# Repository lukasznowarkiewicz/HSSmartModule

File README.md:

# HSSmartModule

## Overview

This repository contains design files of Home Span Smart Module. The device is intended to use with existing electrical installation as a light controller. Initially intended to be flashed with Home Span firmware and  use with Apple Home Kit ecosystem. This will allow basic support of the implement features like outputs control, reading states form the inputs and control from other devices - aka smart home in-wall module functionality. This will allow rather quick start of the desting of the device in the files and give chance to spot potential problems right away. In the future it is planned to create custom application, with support for all implemented features in hardware like power measurement, input from presence sensor and enabling thread radio communication. The device intentionally is divided into two PCBs. This will allow independent testing, of high voltage and low voltage parts. In the future will be possible to replace low voltage PCB with with another variant - equiped with another MCU, for example NRF52840. In the future after initial bringup, set of boards could be easily redesigned as single rigid-flex PCB. 

## Features

- Powered form 230VAC mains voltage
- 2x output for controlling 230VAC devices, up to 4A per channel
- 3x 230VAC inputs - two intended for ordinary switches for direct control of the outputs, additional input for motion or presence sensor
- Power usage measurement using CS5480
- ESP32-C6 SOC as main MCU and radio module
- 8MB SPI flash memory 
- Wi-Fi 6, Bluetooth 5 LE, Thread (802.15.4), Zigbee
- U.FL antenna connector

## Block diagram

## Low Voltage PCB

### LVPCB Schematic

- 3V3 power input - board is powered from HVPCB, or from programmer. If HVPCB is supplying power, 3V3 power jumper on HSSM-Prog should be left unconnected. 

- ESP32-C6 microcontroller - controlls outputs, reads values from inputs, controlls LEDs and communicate with other devices over thread, zigbee or wifi. All power inputs, crystal oscillator circuit, connection to SPI flash implemented according to datasheet.

- Antenna connector - allow connecting external 2.4 GHz antenna for wirelless connectivity

- SPI flash memory - stores ESP32-C6 program

- Additional switches and outs for debug - as program development with board powered from 230VAC seems risky, added additional switches and LEDs representing inputs and outputs on HVPCB. With those program development is possible, even without HVPCB, while LVPCB beeing powered from 3V3 LDO on programming board. 

- Programming connector - to connect HSSM-Prog, enables UART communication and puting ESP32-C6 into programming mode

- Edge connector - allows HSSM-FCB to be soldered to and connect HVPCB

## High Voltage PCB

<!-- 

 -->

Features:
- Outputs controls - two relays for switching 230VAC loads, internally connected to live wire terminal. Both relays powered from 12V 

- Input switches - three 230VAC inputs - for 

- 230VAC to 12VDC

- 12VDC to 3V3VDC converter

- Power measurement

## Flexible circuit board

## HSSmartModule Programmer

Features
- CP2102N USB UART converter
- Automatically put ESP32 chips into programming mode 
- power supply and data lines insulation 
- 6 poles 1.27 mm header and 6 poles 2.54 mm header for programming
- 3V3 voltage supplied to target MCU can be disable by removal of the jumper

## Manufacturing

All PCBs manufactured by JLCPCB, according to stackup set in each board's project.  

### HSSM-Prog

### HSSM-LVPCB

### HSSM-HVPCB

## Boards bring up 

## HSSM device assembly

### Firmware for boards testing

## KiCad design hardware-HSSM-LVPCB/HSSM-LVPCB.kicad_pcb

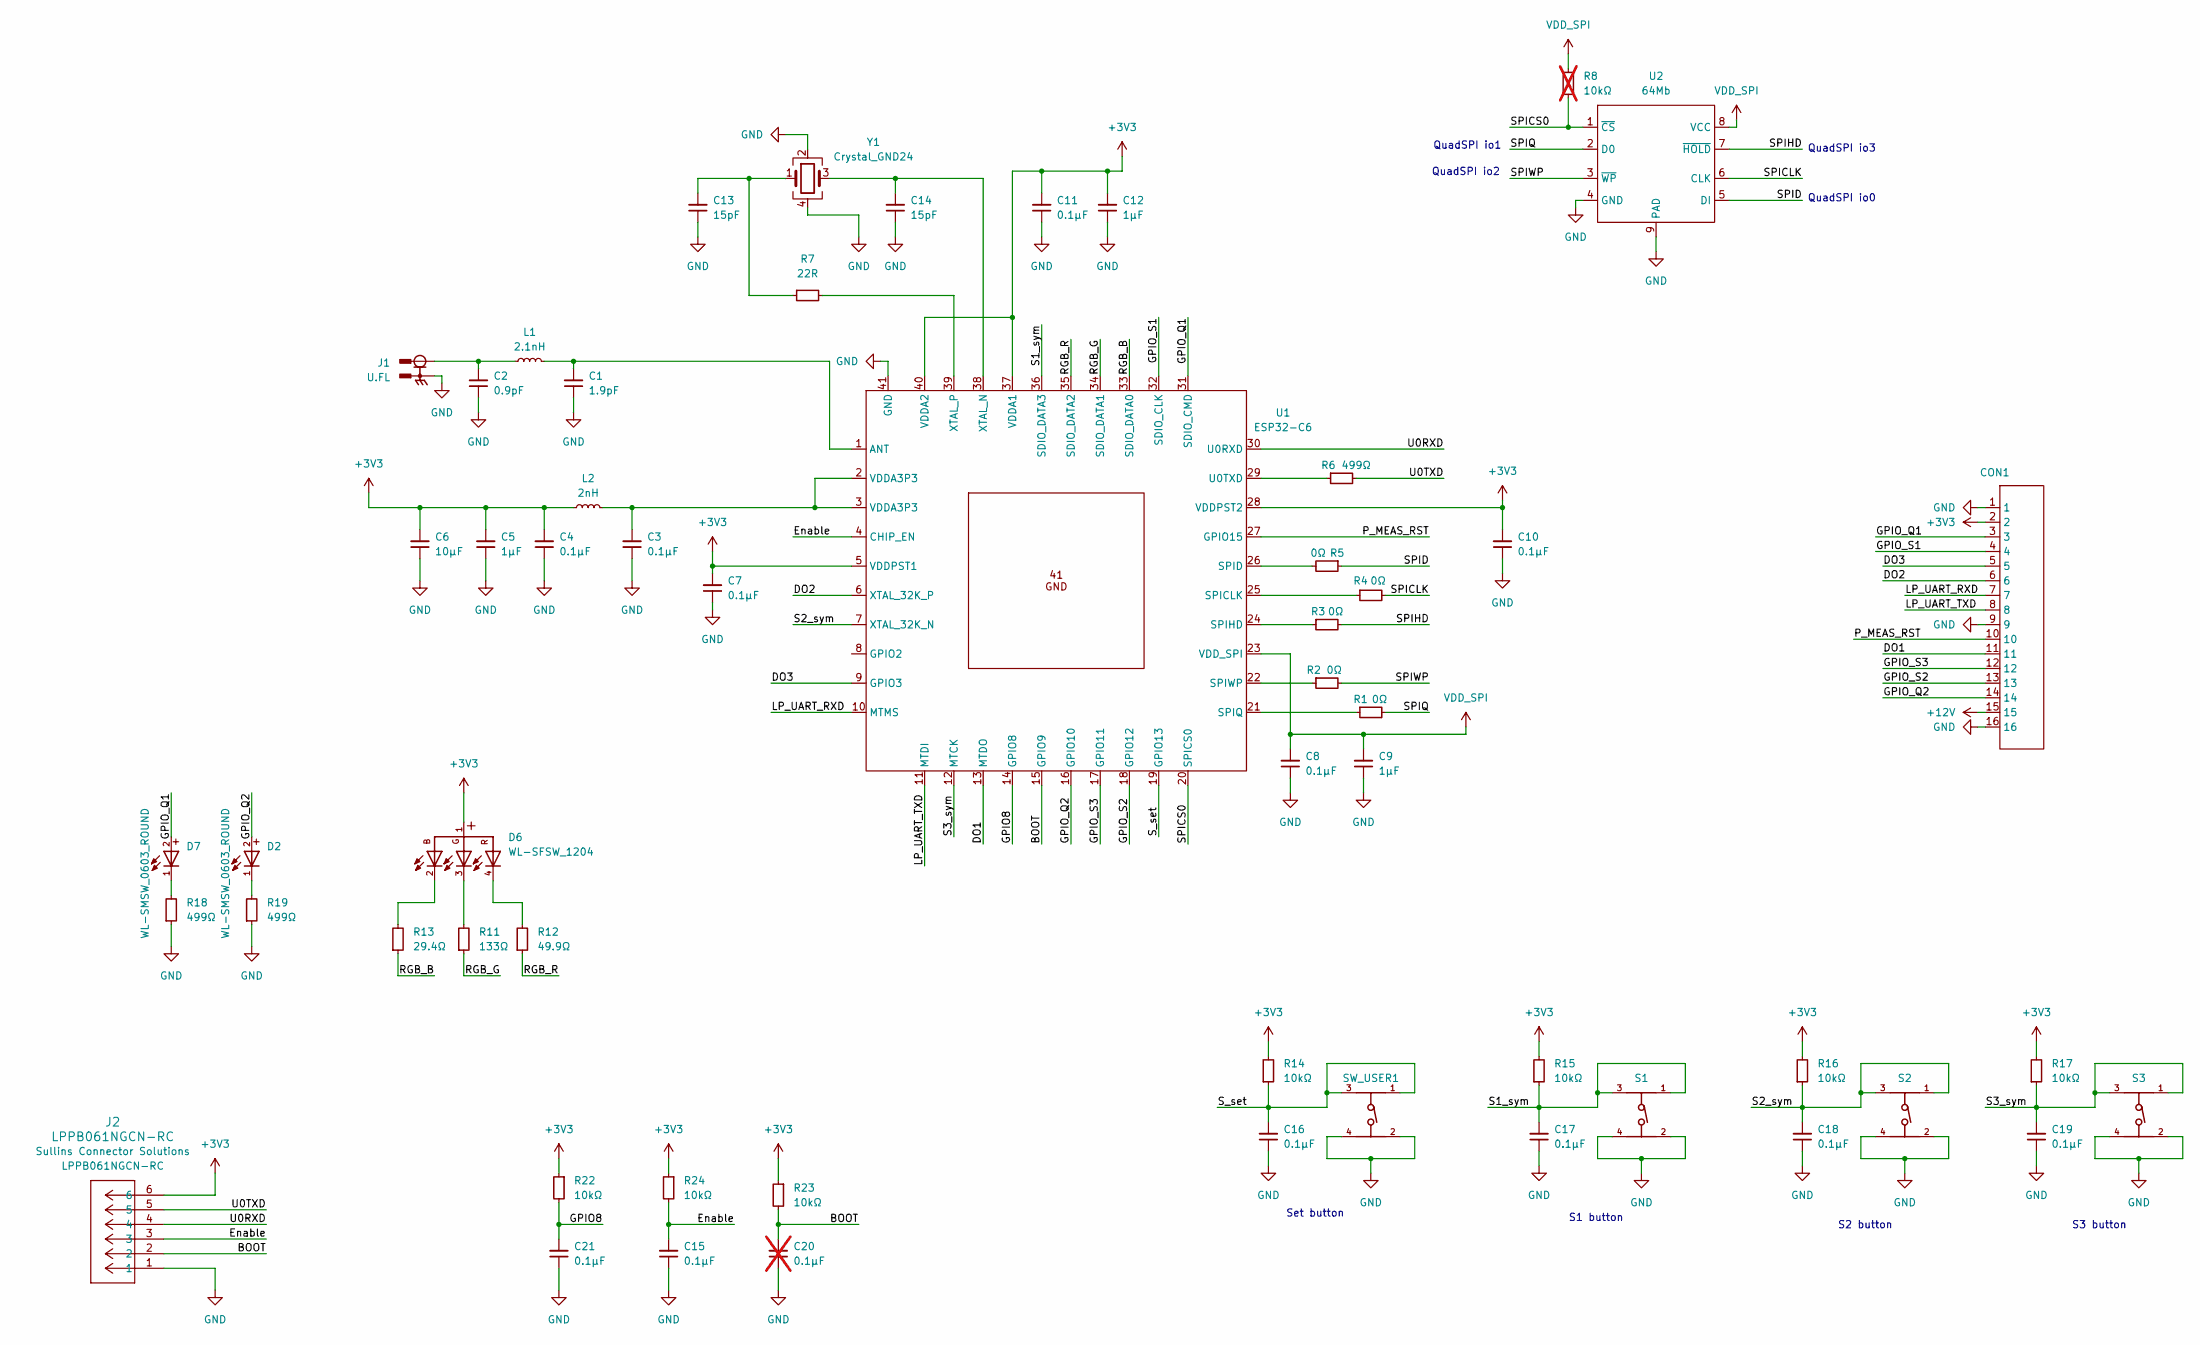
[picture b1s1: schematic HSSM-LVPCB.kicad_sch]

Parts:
C1: C_1p9_0.05pct_50V_0201_GRM0335C1H1R9WA01D; C_0201; MPN GRM0335C1H1R9WA01D
C2: C_0p9_0.05pct_50V_0201_GRM0335C1HR90WA01D; C_0201; MPN GRM0335C1HR90WA01D
C3, C4, C7, C8, C10, C11, C15, C16, C17, C18, C19, C21: C_0u1_10pct_50V_0402_GRM155R71H104KE14D; C_0402; MPN GRM155R71H104KE14D
C5, C9, C12: C_1uF_10pct_16V_0603_GCM188R71C105KA64D; C_0603; MPN GCM188R71C105KA64D
C6: C_10u_20pct_16V_0603_GRM188R61C106MA73D; C_0603; MPN GRM188R61C106MA73D
C13, C14: C_15pF_1pct_50V_0402_C0402C150F5GACAUTO; C_0402; MPN C0402C150F5GACAUTO
C20: C_0u1_10pct_50V_0402_GRM155R71H104KE14D; C_0402; MPN GRM155R71H104KE14D; not fitted
CON1: FFC_solder_connector_16pos
D2, D7: WL-SMSW_0603_ROUND; 155060AS73200; MPN 155060AS73200
D6: WL-SFSW_1204; 155124M173200; MPN 155124M173200
J1: UFL_R_SMT_1_10; CONMHF1-SMD-T; MPN U.FL-R-SMT-1(10)
J2: LPPB061NGCN-RC; MPN LPPB061NGCN-RC
L1: L_2n1_2000mA_0201_LQP03HQ2N1B02D; L_0201; MPN LQP03HQ2N1B02D
L2: L_2nH_0402_ MHQ1005075HA2N0BTD25; L_0402; MPN MHQ1005075HA2N0BTD25
R1, R2, R3, R4, R5: R_0R_5pct_0402_RC0402JR-070RL; R_0402; MPN RC0402JR-070RL
R6, R18, R19: R_499R_1pct_0402_RC0402FR-07499RL; R_0402; MPN RC0402FR-07499RL
R7: R_22R_1pct_0402_CRCW040222R0FKED; R_0402; MPN CRCW040222R0FKED
R8: R_10k_1pct_0402_RC0402FR-0710KL; R_0402; MPN RC0402FR-0710KL; not fitted
R11: R_133R_1pct_0402_CRCW0402133RFKED; R_0402; MPN CRCW0402133RFKED
R12: R_49R9_1pct_0402_CRCW040249R9FKED; R_0402; MPN CRCW040249R9FKED
R13: R_29R4_1pct_0402_CRCW040229R4FKED; R_0402; MPN CRCW040229R4FKED
R14, R15, R16, R17, R22, R23, R24: R_10k_1pct_0402_RC0402FR-0710KL; R_0402; MPN RC0402FR-0710KL
S1, S2, S3: 434331045822; MPN 434331045822
SW_USER1: 434331045822; MPN 434331045822
U1: ESP32-C6; QFN-40-1EP_5x5mm_P0.4mm_EP3.6x3.6mm; MPN ESP32-C6
U2: W25Q64JVZPIM_WSON-8; WSON-8-1EP_6x5mm_P1.27mm_EP3.4x4.3mm; MPN W25Q64JVZPIM
Y1: Crystal_GND24; Crystal_SMD_2016-4Pin_2.0x1.6mm; MPN CN4040M00010001

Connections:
+3V3: C4.2, C5.2, C6.2, C7.2, C10.2, C11.2, C12.2, CON1.2, D6.1, J2.6, L2.1, R14.2, R15.2, R16.2, R17.2, R22.1, R23.1, R24.1, U1.5 (VDDPST1), U1.28 (VDDPST2), U1.37 (VDDA1), U1.40 (VDDA2)
+12V: CON1.15
/BOOT: C20.2, J2.2, R23.2, U1.15 (GPIO9)
/DO1: CON1.11, U1.13 (MTDO)
/DO2: CON1.6, U1.6 (XTAL_32K_P)
/DO3: CON1.5, U1.9 (GPIO3)
/Enable: C15.2, J2.3, R24.2, U1.4 (CHIP_EN)
/GPIO8: C21.2, R22.2, U1.14 (GPIO8)
/GPIO_Q1: CON1.3, D7.2, U1.31 (SDIO_CMD)
/GPIO_Q2: CON1.14, D2.2, U1.16 (GPIO10)
/GPIO_S1: CON1.4, U1.32 (SDIO_CLK)
/GPIO_S2: CON1.13, U1.18 (GPIO12)
/GPIO_S3: CON1.12, U1.17 (GPIO11)
/LP_UART_RXD: CON1.7, U1.10 (MTMS)
/LP_UART_TXD: CON1.8, U1.11 (MTDI)
/P_MEAS_RST: CON1.10, U1.27 (GPIO15)
/RGB_B: R13.1, U1.33 (SDIO_DATA0)
/RGB_G: R11.1, U1.34 (SDIO_DATA1)
/RGB_R: R12.1, U1.35 (SDIO_DATA2)
/S1_sym: C17.2, R15.1, S1.1, S1.3, U1.36 (SDIO_DATA3)
/S2_sym: C18.2, R16.1, S2.1, S2.3, U1.7 (XTAL_32K_N)
/S3_sym: C19.2, R17.1, S3.1, S3.3, U1.12 (MTCK)
/SPICLK: R4.2, U2.6 (CLK)
/SPICS0: R8.1, U1.20 (SPICS0), U2.1 (~CS)
/SPID: R5.1, U2.5 (DI)
/SPIHD: R3.2, U2.7 (~HOLD)
/SPIQ: R1.2, U2.2 (D0)
/SPIWP: R2.2, U2.3 (~WP)
/S_set: C16.2, R14.1, SW_USER1.1, SW_USER1.3, U1.19 (GPIO13)
/U0RXD: J2.4, U1.30 (U0RXD)
/U0TXD: J2.5, R6.2
GND: C1.1, C2.1, C3.1, C4.1, C5.1, C6.1, C7.1, C8.1, C9.1, C10.1, C11.1, C12.1, C13.1, C14.1, C15.1, C16.1, C17.1, C18.1, C19.1, C20.1, C21.1, CON1.1, CON1.9, CON1.16, J1.S1, J1.S2, J1.S3, J2.1, R18.1, R19.1, S1.2, S1.4, S2.2, S2.4, S3.2, S3.4, SW_USER1.2, SW_USER1.4, U1.41 (GND), U2.4 (GND), U2.9 (PAD), Y1.2, Y1.4
unnamed: C2.2, J1.1, L1.1
unnamed: C3.2, L2.2, U1.2 (VDDA3P3), U1.3 (VDDA3P3)
unnamed: C13.2, R7.1, Y1.1
unnamed: D2.1, R19.2
unnamed: D6.2, R13.2
unnamed: D6.3, R11.2
unnamed: D6.4, R12.2
unnamed: D7.1, R18.2
unnamed: C1.2, L1.2, U1.1 (ANT)
unnamed: R4.1, U1.25 (SPICLK)
unnamed: R5.2, U1.26 (SPID)
unnamed: R3.1, U1.24 (SPIHD)
unnamed: R1.1, U1.21 (SPIQ)
unnamed: R2.1, U1.22 (SPIWP)
unnamed: R6.1, U1.29 (U0TXD)
unnamed: C14.2, U1.38 (XTAL_N), Y1.3
unnamed: R7.2, U1.39 (XTAL_P)
VDD_SPI: C8.2, C9.2, R8.2, U1.23 (VDD_SPI), U2.8 (VCC)

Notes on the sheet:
QuadSPI io3
Set button
S1 button
QuadSPI io2
QuadSPI io1
QuadSPI io0
S2 button
S3 button

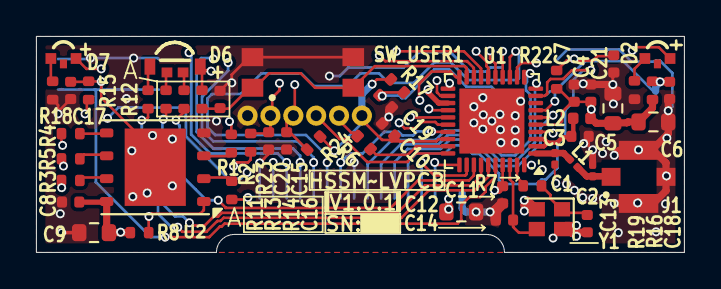
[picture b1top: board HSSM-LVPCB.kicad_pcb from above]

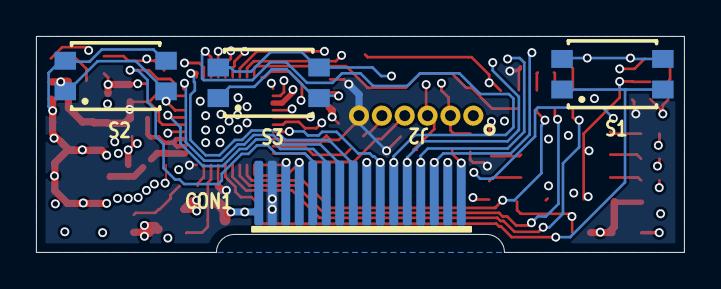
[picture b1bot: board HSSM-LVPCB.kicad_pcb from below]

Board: 4 copper layers, 36.0 x 12.0 mm, 56 parts (5 on the bottom side), 49 nets.

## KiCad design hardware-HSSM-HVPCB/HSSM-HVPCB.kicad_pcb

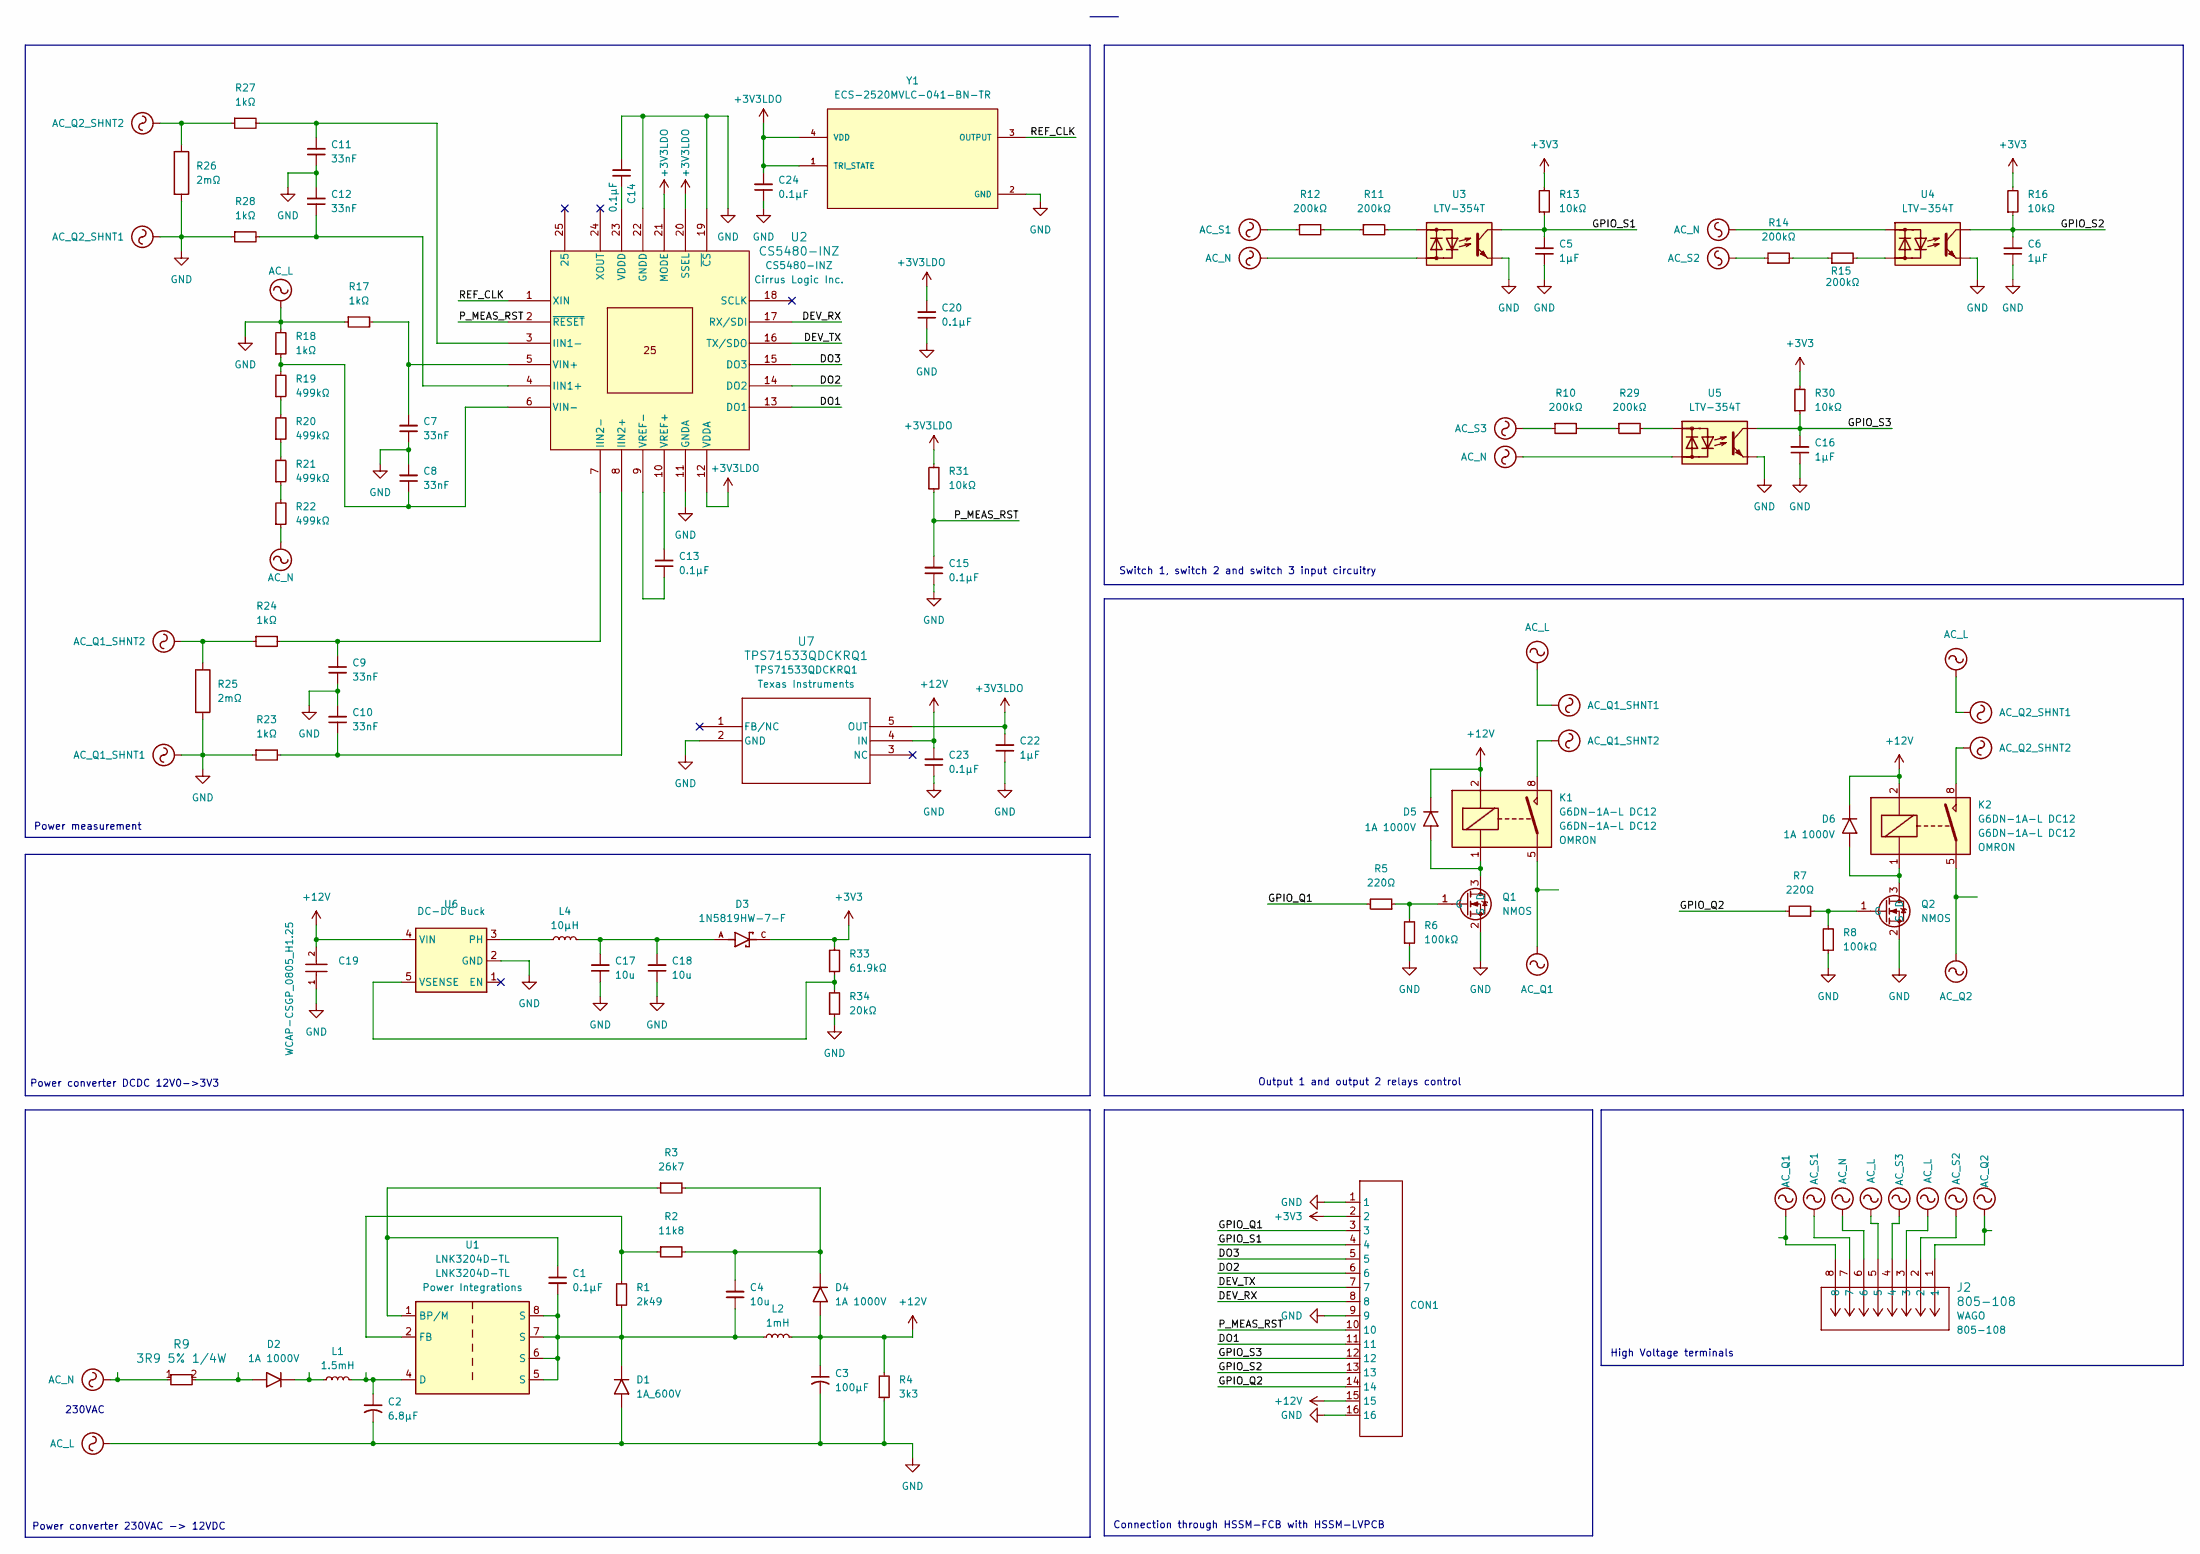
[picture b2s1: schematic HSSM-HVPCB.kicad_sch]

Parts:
C1: C_0u1_10pct_16V_0402_GRM155R71C104KA88J; C_0402; MPN GRM155R71C104KA88J
C2: C_6u8_20pct_400V_8mm_WCAP-ATG5_860021374009; 860021374009; MPN 860021374009
C3: C_100uF_20pct_16V_5mm_WCAP-ATG5_860020372006; 860020372006; MPN 860020372006
C4, C17, C18: C_10u_10pct_25V_0603_GRM188R61E106KA73D; C_0603; MPN GRM188R61E106KA73D
C5, C6, C16, C22: C_1uF_10pct_16V_0603_GCM188R71C105KA64D; C_0603; MPN GCM188R71C105KA64D
C7, C8, C9, C10, C11, C12: C_33nF_10pct_50V_0402_CC0402KRX7R9BB333; C_0402; MPN CC0402KRX7R9BB333
C13, C14, C15, C20, C23, C24: C_0u1_10pct_50V_0402_GRM155R71H104KE14D; C_0402; MPN GRM155R71H104KE14D
C19: WCAP-CSGP_0805_H1.25; 885012107018; MPN 885012107018
CON1: FFC_solder_connector_16pos
D1: D_rect_1A_600V_SOD123FL_ERL1J; D_SOD123FL; MPN ERL1J
D2, D4, D5, D6: D_rect_1A_1000V_SOD123_1N4007W; D_SOD123; MPN 1N4007W
D3: 1N5819HW-7-F; PARTREV 18-2
J2: 805-108; MPN 805-108
K1, K2: G6DN-1A-L DC12; RELAY_G6DN-1A_OMR; MPN G6DN-1A-L DC12
L1: L_1.5mH_20pct_1500uH_LPS4012-155MRC; LPS4012; MPN LPS4012-155MRC
L2: L_1mH_10pct_SDR0503-102KL; SDR0503; MPN SDR0503-102KL
L4: L_10uH_20pct_1A_SDCL1V3012-100M-R; L_3012; MPN SDCL1V3012-100M-R
Q1, Q2: Q_NMOS_SOT-23_IRLML6344; SOT-23; MPN IRLML6344
R1: R_2k49_1pct_0402_RC0402FR-072K49L; R_0402; MPN RC0402FR-072K49L
R2: R_11k8_1pct_0402_RC0402FR-0711K8L; R_0402; MPN RC0402FR-0711K8L
R3: R_26k7_0.1pct_0402_CPF0402B26K7E1; R_0402; MPN CPF0402B26K7E1
R4: R_3k3_5pct_0402_RC0402JR-073K3L; R_0402; MPN RC0402JR-073K3L
R5, R7: R_220R_1pct_0402_RC0402FR-07220RL; R_0402; MPN RC0402FR-07220RL
R6, R8: R_100k_1pct_0402_RC0402FR-07100KL; R_0402; MPN RC0402FR-07100KL
R9: 3R9 5% 1/4W; LCM0207B03908JBP00; MPN LCM0207B03908JBP00
R10, R11, R12, R14, R15, R29: R_200k_0.1pct_1206_VT1206BRD07200KL; R_1206_HV; MPN VT1206BRD07200KL
R13, R16, R30, R31: R_10k_1pct_0402_RC0402FR-0710KL; R_0402; MPN RC0402FR-0710KL
R17, R18, R23, R24, R27, R28: R_1k_1pct_0402_CRCW04021K00FKED; R_0402; MPN CRCW04021K00FKED
R19, R20, R21, R22: R_499k_1pct_1206_KTR18EZPF4993; R_1206_HV; MPN KTR18EZPF4993
R25, R26: R_Shunt_2mOhm_1pct_1210_PMR25HZPFV2L00; R_1210; MPN PMR25HZPFV2L00
R33: R_61k9_1pct_0402_RC0402FR-0761K9L; R_0402; MPN RC0402FR-0761K9L
R34: R_20k_1pct_0402_RC0402FR-0720KL; R_0402; MPN RC0402FR-0720KL
U1: LNK3204D-TL; PowerIntegrations_SO-8C; MPN LNK3204D-TL
U2: CS5480-INZ; CIR-QFN-24; MPN CS5480-INZ
U3, U4, U5: LTV-354T; MPN LTV-354T
U6: TPS560200DBVR_SOIC_6_TI; SOIC_6; MPN TPS560200DBVR
U7: TPS71533QDCKRQ1; MPN TPS71533QDCKRQ1
Y1: ECS-2520MVLC-041-BN-TR; MPN ECS-2520MVLC-041-BN-TR

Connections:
+3V3: CON1.2, D3.C, R13.2, R16.2, R30.2, R33.2
+3V3LDO: C20.2, C22.2, C24.2, R31.2, U2.12 (VDDA), U2.20 (SSEL), U2.21 (MODE), U7.5 (OUT), Y1.1 (TRI_STATE), Y1.4 (VDD)
+12V: C3.1, C19.2, C23.2, CON1.15, D4.2 (A), D5.1 (K), D6.1 (K), K1.2, K2.2, L2.2, R4.2, U6.4 (VIN), U7.4 (IN)
/DEV_RX: CON1.8, U2.17 (RX/SDI)
/DEV_TX: CON1.7, U2.16 (TX/SDO)
/DO1: CON1.11, U2.13 (DO1)
/DO2: CON1.6, U2.14 (DO2)
/DO3: CON1.5, U2.15 (DO3)
/GPIO_Q1: CON1.3, R5.2
/GPIO_Q2: CON1.14, R7.2
/GPIO_S1: C5.2, CON1.4, R13.1, U3.4 (R)
/GPIO_S2: C6.2, CON1.13, R16.1, U4.4 (R)
/GPIO_S3: C16.2, CON1.12, R30.1, U5.4 (R)
/P_MEAS_RST: C15.2, CON1.10, R31.1, U2.2 (~RESET)
/REF_CLK: U2.1 (XIN), Y1.3 (OUTPUT)
AC_L: C2.2, C3.2, C5.1, C6.1, C7.1, C8.2, C9.1, C10.2, C11.1, C12.2, C14.2, C15.1, C16.1, C17.1, C18.1, C19.1, C20.1, C22.1, C23.1, C24.1, CON1.1, CON1.9, CON1.16, D1.2 (A), J2.3, J2.5, Q1.2 (S), Q2.2 (S), R4.1, R6.1, R8.1, R17.1, R18.2, R23.1, R25.1, R26.1, R28.1, R34.1, U2.11 (GNDA), U2.19 (~CS), U2.22 (GNDD), U3.3 (R), U4.3 (R), U5.3 (R), U6.2 (GND), U7.2 (GND), Y1.2 (GND)
AC_N: J2.6, R9.1, R22.1, U3.2 (K), U4.1 (A), U5.2 (K)
AC_Q1: J2.8, K1.5
AC_Q1_SHNT2: K1.8, R24.1, R25.2
AC_Q2: J2.1, K2.5
AC_Q2_SHNT2: K2.8, R26.2, R27.1
AC_S1: J2.7, R12.1
AC_S2: J2.2, R14.1
AC_S3: J2.4, R10.1
unnamed: C17.2, C18.2, D3.A, L4.2
unnamed: C1.2, C4.1, D1.1 (K), L2.1, R1.1, U1.5 (S), U1.6 (S), U1.7 (S), U1.8 (S)
unnamed: D2.2 (A), R9.2
unnamed: D2.1 (K), L1.1
unnamed: C4.2, D4.1 (K), R2.2, R3.2
unnamed: D5.2 (A), K1.1, Q1.3 (D)
unnamed: D6.2 (A), K2.1, Q2.3 (D)
unnamed: Q1.1 (G), R5.1, R6.2
unnamed: Q2.1 (G), R7.1, R8.2
unnamed: R10.2, R29.1
unnamed: R11.1, R12.2
unnamed: R14.2, R15.1
unnamed: R19.1, R20.2
unnamed: R20.1, R21.2
unnamed: R21.1, R22.2
unnamed: C1.1, R3.1, U1.1 (BP/M)
unnamed: C2.1, L1.2, U1.4 (D)
unnamed: R1.2, R2.1, U1.2 (FB)
unnamed: C12.1, R28.2, U2.4 (IIN1+)
unnamed: C11.2, R27.2, U2.3 (IIN1-)
unnamed: C10.1, R23.2, U2.8 (IIN2+)
unnamed: C9.2, R24.2, U2.7 (IIN2-)
unnamed: C14.1, U2.23 (VDDD)
unnamed: C7.2, R17.2, U2.5 (VIN+)
unnamed: C8.1, R18.1, R19.2, U2.6 (VIN-)
unnamed: C13.2, U2.10 (VREF+)
unnamed: C13.1, U2.9 (VREF-)
unnamed: R11.2, U3.1 (A)
unnamed: R15.2, U4.2 (K)
unnamed: R29.2, U5.1 (A)
unnamed: L4.1, U6.3 (PH)
unnamed: R33.1, R34.2, U6.5 (VSENSE)

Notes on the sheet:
Output 1 and output 2 relays control
High Voltage terminals
Power measurement
230VAC
Connection through HSSM-FCB with HSSM-LVPCB
Power converter DCDC 12V0->3V3
Power converter 230VAC -> 12VDC
Switch 1, switch 2 and switch 3 input circuitry

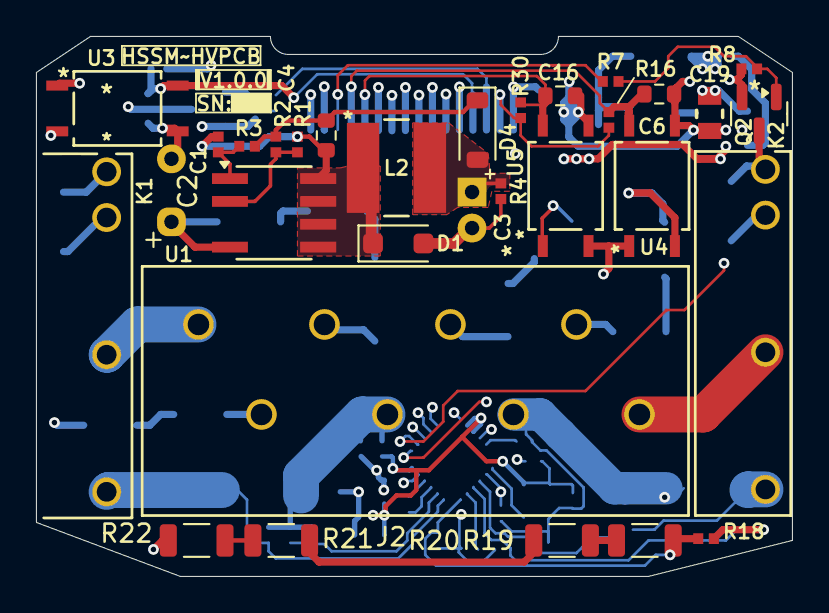
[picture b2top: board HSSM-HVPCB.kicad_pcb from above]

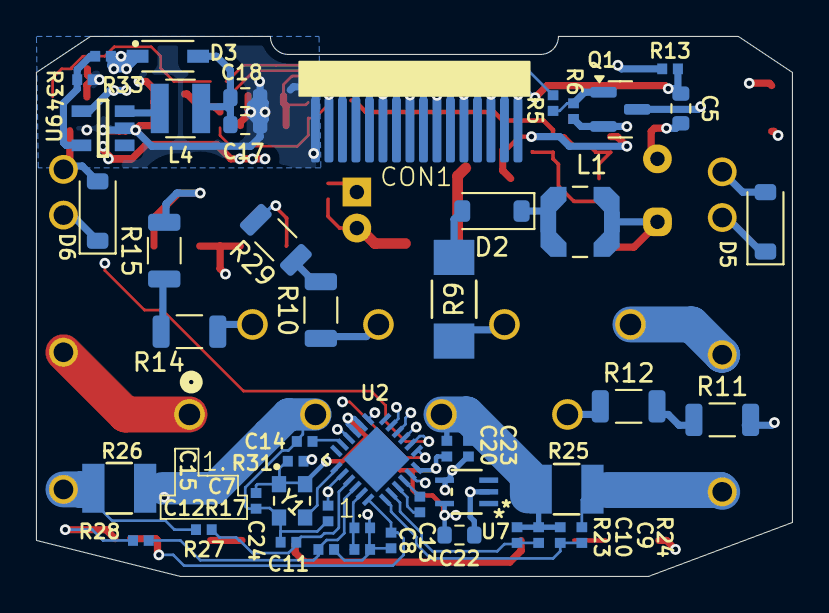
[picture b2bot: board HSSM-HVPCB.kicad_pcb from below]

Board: 4 copper layers, 42.0 x 30.0 mm, 79 parts (48 on the bottom side), 56 nets.

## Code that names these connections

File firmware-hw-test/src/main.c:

// ###### - Imports - ###### 
#include <stdio.h>
#include "freertos/FreeRTOS.h"
#include "freertos/task.h"
#include "driver/gpio.h"

// ###### - GPIOs config - ###### 
#define PIN_D01         GPIO_NUM_7
#define PIN_D02         GPIO_NUM_0
#define PIN_D03         GPIO_NUM_3
#define PIN_LP_UART_RXD GPIO_NUM_10
#define PIN_LP_UART_TXD GPIO_NUM_11

#define PIN_GPIO_Q1     GPIO_NUM_18
#define PIN_GPIO_Q2     GPIO_NUM_10

#define PIN_S1_sym      GPIO_NUM_23
#define PIN_S2_sym      GPIO_NUM_1
#define PIN_S3_sym      GPIO_NUM_6

#define PIN_GPIO_S1     GPIO_NUM_19
#define PIN_GPIO_S2     GPIO_NUM_12
#define PIN_GPIO_S3     GPIO_NUM_5
#define PIN_S_set       GPIO_NUM_7

#define PIN_RGB_R       GPIO_NUM_22
#define PIN_RGB_G       GPIO_NUM_21
#define PIN_RGB_B       GPIO_NUM_20


// ###### - Main loop - ###### 
void app_main(void)
{
    // Configure the GPIOs
    gpio_reset_pin(PIN_S1_sym);
    gpio_reset_pin(PIN_S2_sym);
    gpio_reset_pin(PIN_S3_sym);
    gpio_set_direction(PIN_S1_sym, GPIO_MODE_INPUT);
    gpio_set_direction(PIN_S2_sym, GPIO_MODE_INPUT);
    gpio_set_direction(PIN_S3_sym, GPIO_MODE_INPUT);


    gpio_reset_pin(PIN_GPIO_Q1);
    gpio_reset_pin(PIN_GPIO_Q2);
    gpio_reset_pin(PIN_RGB_R);
    gpio_reset_pin(PIN_RGB_G);
    gpio_reset_pin(PIN_RGB_B);
    gpio_set_direction(PIN_GPIO_Q1, GPIO_MODE_OUTPUT);
    gpio_set_direction(PIN_GPIO_Q2, GPIO_MODE_OUTPUT);
    gpio_set_direction(PIN_RGB_R, GPIO_MODE_OUTPUT);
    gpio_set_direction(PIN_RGB_G, GPIO_MODE_OUTPUT);
    gpio_set_direction(PIN_RGB_B, GPIO_MODE_OUTPUT);


    gpio_set_level(PIN_RGB_R, 0);
    gpio_set_level(PIN_RGB_G, 0);
    gpio_set_level(PIN_RGB_B, 0);
    gpio_set_level(PIN_GPIO_Q1, 1);
    gpio_set_level(PIN_GPIO_Q2, 1);

    vTaskDelay(1000);

    while (1) {
        if(gpio_get_level(PIN_S1_sym)){
            gpio_set_level(PIN_GPIO_Q1, 1);
        }else{
            gpio_set_level(PIN_GPIO_Q1, 0);
        }

        if(gpio_get_level(PIN_S2_sym)){
            gpio_set_level(PIN_GPIO_Q2, 1);
        }else{
            gpio_set_level(PIN_GPIO_Q2, 0);
        }

        if(gpio_get_level(PIN_S3_sym)){
            gpio_set_level(PIN_RGB_R, 1);
            gpio_set_level(PIN_RGB_G, 1);
            gpio_set_level(PIN_RGB_B, 1);
        }else{
            gpio_set_level(PIN_RGB_R, 0);
            gpio_set_level(PIN_RGB_G, 0);
            gpio_set_level(PIN_RGB_B, 0);
        }

    }
}

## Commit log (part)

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2024-12-05 [#3] Add CS5480-INZ power meter
2024-12-05 [#3] Add components to schematic
2024-12-06 Update gitignore
2024-12-06 [#3] Add resistors
2024-12-06 [#3] Add GRM155R71C104KA88J
2024-12-06 [#3] Correct GRM155R71C104KA88J
2024-12-06 [#3] Correct GRM155R71H104KE14D
2024-12-09 [#3] Update GRM155R71C104KA88J
2024-12-09 [#3] Update GRM155R71H104KE14D
2024-12-09 [#3] Remove debug component
2024-12-09 [#3] Update CRCW04021K43FKED
2024-12-09 [#3] Update RC0402JR-073K3L
2024-12-09 [#3] Update RR02J10RTB
2024-12-09 [#3] Add 1N4007W
2024-12-09 [#3] Add 860021374009
2024-12-09 [#3] Update 860021374009
2024-12-09 [#3] Add 860020372006
2024-12-09 [#3] Add LPS4012-155MRC
2024-12-09 [#3] Add SDR0503-102KL
2024-12-09 [#3] Add MURS160-E3/52T
2024-12-09 [#3] Add RC0402FR-072K49L
2024-12-09 [#3] Add CPF0402B26K7E1
2024-12-09 [#3] SCH LNK3204 connections WIP
2024-12-09 [#3] Add GRM188R61E106KA73D
2024-12-09 [#3] SCH LNK3204 connections
2024-12-09 [#3] SCH LNK3204 connections correct output capacitor connection
2024-12-09 [#3] Correct MURS160-E3/52T
2024-12-09 [#3] Add RC0402FR-07220RL
2024-12-09 [#3] Add RC0402FR-07100KL
2024-12-09 [#3] Add IRLML6344
2024-12-09 [#3] Add APHHS1005CGCK
2024-12-09 [#3] SCH add relay control
2024-12-10 [#3] Add 3404.2422.11
2024-12-10 [#3] SCH relay output
2024-12-10 [#3] SCH add relay status leds
2024-12-10 [#3] Correct LNK3204D-TL symbol MPN
2024-12-10 [#3] Add LTV-354T
2024-12-10 [#3] Add VT1206BRD07200KL
2024-12-10 [#3] Add RC0402FR-0710KL
2024-12-10 [#3] Add GCM188R71C105KA64D
2024-12-10 [#3] Correct LTV-354T
2024-12-10 [#3] Add HV output terminals connections proposition
2024-12-12 [#3] Correct CS5480
2024-12-12 [#3] Add CRE2512-FZ-R002E-3
2024-12-12 [#3] Add CC0402KRX7R9BB333
2024-12-12 [#3] Add CRCW04021K00FKED
2024-12-12 [#3] Add KTR18EZPF4993
2024-12-12 [#3] SCH power measuring - voltage measure
2024-12-12 [#3] SCH power measuring - current measure on CH1
2024-12-12 [#3] SCH power measuring - current measure on CH2
2024-12-12 [#3] SCH power measuring - connect power pins
2024-12-12 [#3] SCH power measuring - add oscillator
2024-12-12 [#3] SCH power measuring - clean up
2024-12-12 [#3] Add 20021311-00010T4LF
2024-12-12 [#3] SCH add connector to LVPCB
2024-12-13 [#3] Add MOV-14D431K
2024-12-13 [#3] SCH add surge protection
2024-12-13 [#4] Add HSSM-LVPCB project
2024-12-13 [#4] Add GRM155R71H104KE14D
2024-12-13 [#4] Add C0402C103K5RACTU
2024-12-13 [#4] Add MLG0402Q2N0ST000
2024-12-13 [#4] Add RC0402FR-0710KL
2024-12-13 [#4] Add RC0402FR-07499RL
2024-12-13 [#4] Add W25Q64JVSSIQ
2024-12-13 [#4] Add ABM8-40.000MHZ-B2-T
2024-12-13 [#4] Add GCM1555C1H270JA16J
2024-12-15 [#3] Add C0402C153K4RACTU
2024-12-15 [#3] Add EMK316BJ475ML
2024-12-15 [#3] Add CRCW04025K60FKED
2024-12-15 [#3] Add STPS5L25B-TR
2024-12-15 [#3] Add CRCW04027K15FKED
2024-12-15 [#3] Add CC1206KKX7R8BB106
2024-12-15 [#3] Add L6902D
2024-12-15 [#3] Add SRN6045-680M
2024-12-15 [#3] Update L6902D
2024-12-15 [#3] Add RLC73N2AR169FTD
2024-12-15 [#3] SCH add 12V0 to 3V3 power converter
2024-12-16 [#3] Add SDCL1V3012-100M-R
2024-12-16 [#3] Add RC0402FR-0761K9L
2024-12-16 [#3] Add RC0402FR-0720KL
2024-12-16 [#3] Add TPS560200DBVR
2024-12-16 [#3] Replace DCDC converter with TPS560200DBVR
2024-12-16 [#4] Add U.FL-R-SMT-1(10)
2024-12-16 [#4] Add GRM0335C1HR90WA01D
2024-12-16 [#4] Add GRM0335C1H1R9WA01D
2024-12-16 [#4] Add LQP03HQ2N1B02D
2024-12-17 [#4] ESP32-C6 WIP
2024-12-17 [#4] Add ESP32-C6
2024-12-17 [#4] SCH ESP32-C6 WIP
2024-12-17 [#4] Add GRM188R61C106MA73D
2024-12-17 [#4] Update W25Q64JVSSIQ
2024-12-18 [#4] Add ECS-2520SMV-400-FN-TR
2024-12-18 [#4] SCH replace crystal oscillator with more stagble one
2024-12-18 [#4] Add CP2102-GMR
2024-12-18 [#4] Add BSS123
2024-12-18 [#4] SCH add USB UART converter as programmer
2024-12-18 [#4] Add SKRPACE010
2024-12-18 [#4] Add MCP9700BT-E/TT
2024-12-18 [#4] Add 20021112-00010T1LF
2024-12-18 [#4] Add 150505M173300
2024-12-19 [#4] Correct 150505M173300
2024-12-20 [#4] Add CRCW0402133RFKED
2024-12-20 [#4] Add CRCW040249R9FKED
2024-12-20 [#4] Add CRCW040229R4FKED
2024-12-20 [#4] SCH add RGB LED
2024-12-21 [#4] SCH add usr btn
2024-12-22 [#4] SCH Add board to board connections
2024-12-22 [#4] Add BME280
2024-12-22 [#4] Add ENS160-BGLM
2024-12-22 [#4] Correct BME280
2024-12-29 [#6] Add footprint LNK3204D-TL
2024-12-29 [#6] Add footprint C 0402
2024-12-29 [#6] Add footprint C 1206
2024-12-29 [#6] Add footprint R 0402
2024-12-29 [#6] Add footprint R 0603
2024-12-29 [#6] Add footprint 860021374009
2024-12-29 [#6] Add footprint 860020372006
2024-12-29 [#6] Add footprint for MURS160-E3/52T
2024-12-29 [#6] Add footprint for 1N4007W
2024-12-29 [#6] Add footprint for STPS5L25B-TR
2024-12-30 [#6] Add footprint for G6DN-1A-L DC12
2024-12-30 [#6] Add footprint for LPS4012-155MRC
2024-12-30 [#6] Add footprint for IRLML6344
2024-12-30 [#6] Add footprint for RR02J10RTB
2024-12-30 [#6] Add footprint for 2086-1103
2024-12-30 [#6] Add footprint for /Users/lukasznowarkiewicz/Downloads/ul_2601-1110/CadenasModel/2601-1110.stp
2024-12-30 [#6] Add footprint for TPS560200DBVR
2024-12-30 [#6] Add footprint for LTV-354T
2024-12-30 [#6] Add footprint for MOV-14D431K
2024-12-30 [#6] BRD import all updated footprints to PCB
2024-12-30 [#6] Update G6DN-1A-L DC12
2024-12-30 [#6] Update 860021374009
2024-12-30 [#6] Update MOV-14D431K
2024-12-30 [#6] Update step models
2024-12-30 [#6] Add step model for SDR0503-102KL
2024-12-30 [#6] Add step model for LPS4012-155MRC
2024-12-30 [#6] Add step model R_0402
2024-12-30 [#6] Add step model C_0402
2024-12-30 [#6] Fix step model R 1206
2024-12-30 [#6] Add board outline
2024-12-30 [#6] Remove 3pin terminal
2024-12-30 [#6] Remove RGB LED
2024-12-30 [#6] Add 2601-3108
2024-12-30 [#6] Add 2601-1108
2024-12-30 [#6] Replace wago terminal with 8 pos variant
2024-12-30 [#7] Components placement WIP
2024-12-31 [#6] Add ECS-2520MVLC-041-BN-TR
2024-12-31 [#6] Replace crystal oscillator
2025-01-02 [#6] Remove status LEDs from HVPCB
2025-01-02 [#6] Add L 3012
2025-01-02 [#6] Add Schurter UMZ250 fuse
2025-01-02 [#3] Remove fuses
2025-01-02 [#7] Placement WIP
2025-01-03 [#4] Add S1, S2, S3 buttons
2025-01-03 [#4] Add green LED
2025-01-03 [#4] Add status LEDs for inputs and outputs
2025-01-03 [#4] Add 4k7 resistor
2025-01-03 [#4] SCH add BME280
2025-01-03 [#4] SCH add ENS160
2025-01-03 [#4] SCH add note for ENS160
2025-01-03 [#4] Add FFC_solder_connector_16pos
2025-01-04 [#4] Replace board-to-board connector
2025-01-04 [#8] Add footprint for ESP32-C6
2025-01-04 [#8] Add SOT-23
2025-01-04 [#8] Add C_0402
2025-01-04 [#8] Add R_0402
2025-01-04 [#8] Update R_0402
2025-01-04 [#8] Add SW_TACT_SKRPACE010
2025-01-04 [#8] Add LED_0603_1608Metric
2025-01-04 [#8] Update footprint library name
2025-01-04 [#8] Add CONMHF1-SMD-T
2025-01-04 [#8] Add L 0201
2025-01-04 [#8] Add C 0603
2025-01-04 [#8] Add SOIC-8_3.9x4.9mm_P1.27mm
2025-01-04 [#8] Add Bosch_LGA-8_2.5x2.5mm_P0.65mm_ClockwisePinNumbering
2025-01-04 [#8] Add XDCR_ENS160-BGLM
2025-01-04 [#8] Add L 0402
2025-01-04 [#8] Add QFN-28-1EP_4x4mm_P0.4mm_EP2.3x2.3mm
2025-01-04 [#8] Add ECS-2520SMV-400-FN-TR
2025-01-04 [#8] Update symbols and import footprints to PCB
2025-01-04 [#9] PCB mockup
2025-01-04 [#7] PCB update outline
2025-01-04 [#4] Add ADUM3160BRWZ
2025-01-04 [#4] Add 155060AS73200
2025-01-04 [#4] Add 434331045822
2025-01-04 [#9] Replace switches
2025-01-04 [#9] Replace LEDs
2025-01-04 [#4] Add TSM-106-01-L-SH
2025-01-06 [#4] Add LPPB061NGCN-RC
2025-01-06 [#9] Add programming connector
2025-01-06 [#2] Mockup of the device
2025-01-06 Add 805-106
2025-01-06 Fix 860021374009
2025-01-07 Add S3
2025-01-07 [#3] Add 885012107018
2025-01-07 [#3] Add 885012106006
2025-01-07 [#3] Correct 885012107018
2025-01-07 [#7] Replace capacitors in DCDC converter
2025-01-08 [#3] SCH connected FCB signals
2025-01-08 [#3] SCH clean up
2025-01-08 [#3] Add LCM0207B03908JBP00
2025-01-08 [#3] SCH replace fusible resistor with SMD
2025-01-09 [#11] Add connector symbol and footprint
2025-01-10 [#11] Footprint add pads on bottom layer, removed solder paste openings
2025-01-10 [#11] Add basic board
2025-01-10 [#11] Add vias for easier soldering and adjusted FCB size
2025-01-10 [#12] PCB Add netclass for high voltage signals
2025-01-10 [#12] PCB Add netclass for high current paths
2025-01-10 [#12] PCB Correct 230VAC clearance setting
2025-01-10 [#12] PCB Routing WIP
2025-01-10 [#12] PCB Add internal power planes
2025-01-10 [#12] PCB Add custom DRC rules for HV internal layers
2025-01-10 [#12] PCB Modify 860021374009 footprint
2025-01-10 [#12] PCB Modify 860020372006 step model
2025-01-10 [#12] PCB Modify 860020372006 footprint
2025-01-10 [#12] PCB Routing power measurement WIP
2025-01-10 [#12] PCB Routing WIP swaped opto insulation HV inputs
2025-01-10 [#12] PCB Routing WIP S1
2025-01-10 [#12] PCB Routing WIP DCDC converter
2025-01-15 [#4] SCH removed additional sensors
2025-01-16 [#4] SCH ESP32-C6 set pins for boot
2025-01-16 [#4] SCH connect GPIOs
2025-01-16 [#9] PCB placement WIP
2025-01-16 [#13] PCB routing WIP flash
2025-01-16 [#13] PCB routing WIP
2025-01-16 [#13] PCB routing WIP ESP32-C6
2025-01-16 [#13] PCB routing WIP decreased size of all vias
2025-01-16 [#13] PCB routing WIP update design rules
2025-01-18 [#13] PCB routing WIP RGB
2025-01-18 [#13] PCB routing WIP GPIO
2025-01-19 Add additional signals to FCB between PCBs
2025-01-19 [#13] PCB routing WIP prog signals
2025-01-19 [#13] PCB routing
2025-01-19 [#12] PCB routing WIP GPIO
2025-01-19 [#12] PCB routing WIP reconnected shunt resistors to better fit layout
2025-01-21 [#13] Add oscillator CN4040M00010001
2025-01-21 [#13] Add capacitor C0402C150F5GACAUTO
2025-01-21 [#13] Add resistor CRCW040222R0FKED
2025-01-21 [#13] Correct crystal
2025-01-21 [#13] Change stackup to JLCPCB - no requirement and correct antenna traces width to match 50ohm
2025-01-21 [#13] PCB DRC WIP
2025-01-21 [#13] PCB WIP designators
2025-01-21 [#13] PCB Add name, version and serial number on silkscreen
2025-01-21 [#13] PCB fix DRC
2025-01-21 Fix outline, add board info and sn on silkscreen
2025-01-21 [#13] PCB minor corrections to traces
2025-01-21 [#13] PCB generate gerber files
2025-01-21 HSSM-FCB increase traces width
2025-01-21 HSSM-FCB add fabrication files
2025-01-22 [#12] Add TPS71533QDCKRQ1
2025-01-22 [#14] SCH Add LDO for powering power measurement IC
2025-01-22 [#14] Add 1N5819HW-7-F
2025-01-22 [#14] SCH add diode on 3V3 DCDC output
2025-01-23 [#15] Mark Boot capacitor as DNP
2025-01-23 [#15] Add GND keep out around quartz
2025-01-23 [#15] Add more GND vias under ESP32-C6 chip
2025-01-23 [#15] Reposition RF RLC to match pi circuit
2025-01-23 [#15] Modify C1 layout as specified in hardware design guide
2025-01-23 [#15] Fix traces around RF part
2025-01-23 [#15] Add keepout and reference plane under U FL connector
2025-01-23 [#15] Place designators
2025-01-23 [#15] Lenght matched SPI lines
2025-01-23 [#15] Removed unecessary GND cutout from U Fl connector
2025-01-23 [#14] WIP fixing DCDC converter placement
2025-01-23 [#14] fix DCDC converter
2025-01-23 [#14] WIP routing power measurement IC
2025-01-23 [#14] WIP placing elements on silkscreen
2025-01-23 [#14] WIP DRC warnings
2025-01-26 [#14] Increase spacing to L1 coil
2025-03-04 Add ECS-2520MVLC-010-BN-TR
2025-03-04 HVPCB replace oscillator
2025-03-06 Replace shunt resistors
2025-03-07 PCB routing power measurement WIP
2025-03-09 PCB DRC WIP
2025-03-09 PCB 499R change footprint to recommended by datasheet
2025-03-09 PCB DRC Errors
2025-03-09 PCB DRC Warnings WIP
2025-03-09 PCB DRC Clear
2025-03-09 Minor fixes to HSSM LVPCB
2025-03-09 HSSM LVPCB production files
2025-03-24 [#16] Add BOMs for rev.1.0.0
2025-06-15 Fix missing 3V3 voltages
2025-06-16 HVPCB Replace D1 diode
2025-06-16 LVPCB replace SPI serial flash
2025-06-16 LVPCB remove unused package
2025-06-17 README Update project description
2025-06-17 Add missing capacitors step models
2025-06-17 Add HSSM-Prog design EasyEda design files and outputs to other formats
2025-06-17 LVPCB add missing step models
2025-06-17 LVPCB bump revision
2025-06-17 LVPCB schematic clean up
2025-06-17 LVPCB fix vias
2025-06-17 HSSM-HVPCB add missing step models
2025-06-18 README describe LVPCB
2025-06-21 Replace WSON-8-1EP_6x5mm_P1_27mm_EP3_4x4_3mm.step to step
2025-06-21 Add assembly cad model
2025-06-21 Add imgaes and renders

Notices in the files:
parts and their libraries:
License: Apache-2.0
